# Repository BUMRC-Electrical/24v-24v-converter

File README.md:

<!-- kicad_template/README.md -->

<div align="center">
    
</div>

## 24V-24V 35 Amp Converter

This repository contains all documentation and files for the custom 24V Converter.

## File Structure

- ```/kicad/``` contains all of the KiCad 10.0 project files
- ```/datasheets/``` contains all of the .pdf files for the important components
- ```/calculations/``` contains significant calculations that led to a component choice or value choice
- ```/cad/``` currently contains no files
- ```24V_BOM.xlsx``` contains all components, quantities, and links to purchase

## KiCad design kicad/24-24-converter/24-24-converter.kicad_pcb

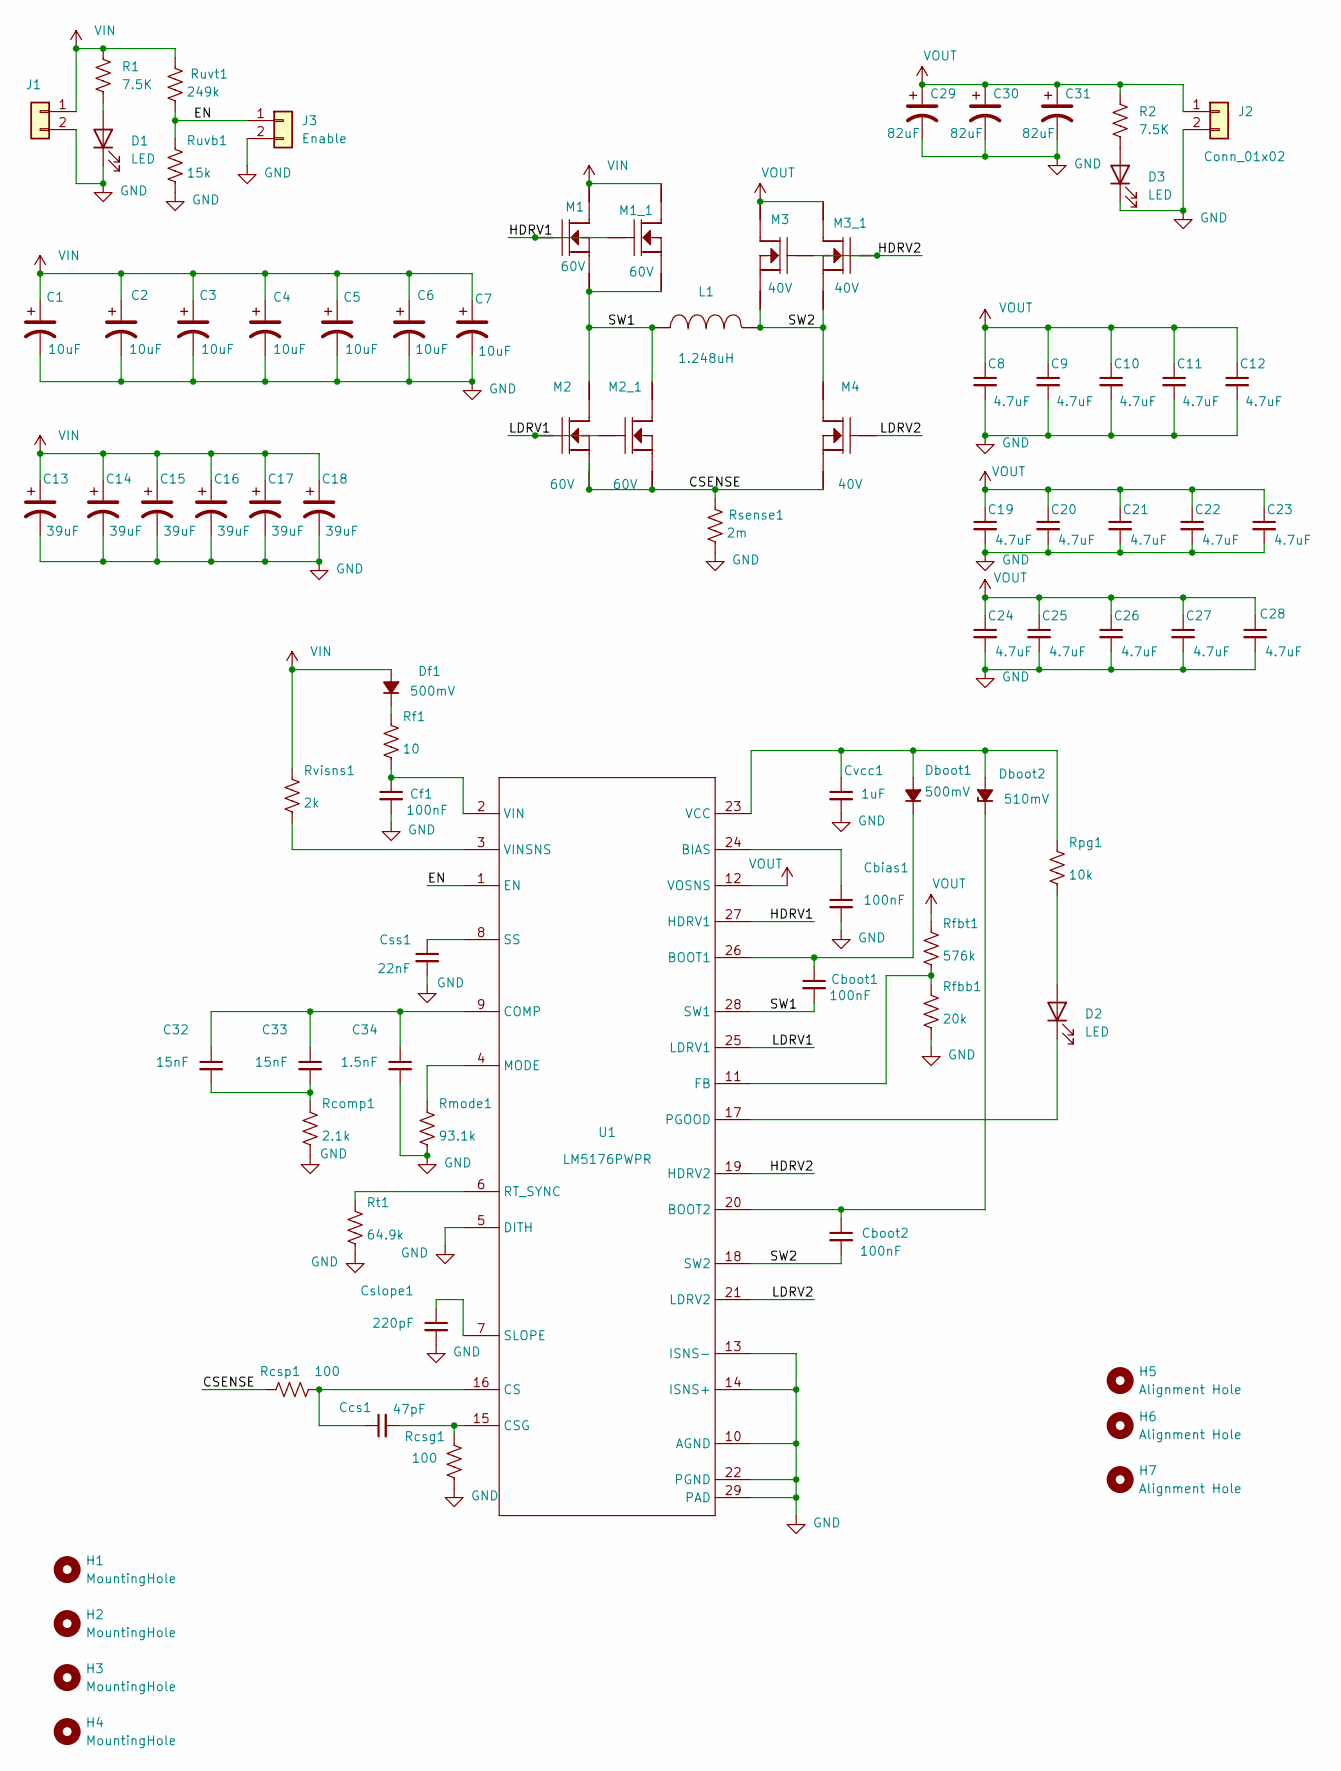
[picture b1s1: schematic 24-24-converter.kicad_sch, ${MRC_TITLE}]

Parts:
C1, C2, C3, C4, C5, C6, C7: 50SVPF10M; Cbulk_CAP_B6-SVPK_PAN; MANUFACTURER PART NUMBER 50SVPF10M
C8, C9, C10, C11, C12, C19, C20, C21, C22, C23, C24, C25, C26, C27, C28: MSASU21GBB5475KTNA01; C_0805_2012Metric_Pad1.18x1.45mm_HandSolder; MANUFACTURER PART NUMBER MSASU21GBB5475KTNA01
C13, C14, C15, C16, C17, C18: 50SVPF39M; Cin_50SVPF39M; MANUFACTURER PART NUMBER 50SVPF39M
C29, C30, C31: 35SVPF82M; PCAP_SVP_E12_PAN; MANUFACTURER PART NUMBER 35SVPF82M
C32, C33: MSASH21GSB7153MTNA01; C_0805_2012Metric_Pad1.18x1.45mm_HandSolder; MANUFACTURER PART NUMBER MSASH21GSB7153MTNA01
C34: GRM2195C1H152JA01D; C_0805_2012Metric_Pad1.18x1.45mm_HandSolder; MANUFACTURER PART NUMBER GRM2195C1H152JA01D
Cbias1: C0805C104M5RACTU; C_0805_2012Metric_Pad1.18x1.45mm_HandSolder; MANUFACTURER PART NUMBER C0805C104M5RACTU
Cboot1, Cboot2: 06033C104KAT2A; C_0805_2012Metric_Pad1.18x1.45mm_HandSolder; MANUFACTURER PART NUMBER 06033C104KAT2A
Ccs1: 06035A470JAT2A; C_0805_2012Metric_Pad1.18x1.45mm_HandSolder; MANUFACTURER PART NUMBER 06035A470JAT2A
Cf1: CGA3E2X7R1H104K080AA; C_0805_2012Metric_Pad1.18x1.45mm_HandSolder; MANUFACTURER PART NUMBER CGA3E2X7R1H104K080AA
Cslope1: CL10C221JB8NNNC; C_0603_1608Metric_Pad1.08x0.95mm_HandSolder; MANUFACTURER PART NUMBER CL10C221JB8NNNC
Css1: C2012C0G1H223K125AA; C_0603_1608Metric_Pad1.08x0.95mm_HandSolder; MANUFACTURER PART NUMBER C2012C0G1H223K125AA
Cvcc1: EMK107B7105KA-T; C_0603_1608Metric_Pad1.08x0.95mm_HandSolder; MANUFACTURER PART NUMBER EMK107B7105KA-T
D1, D2, D3: LED; LED_1206_3216Metric_Pad1.42x1.75mm_HandSolder
Dboot1: GENERIC_DIODE; Diode_BAS16HT1G; MANUFACTURER PART NUMBER GENERIC_DIODE
Dboot2: CDBK0540-HF; Shottkey_MBR0540-TP; MANUFACTURER PART NUMBER CDBK0540-HF
Df1: GENERIC_DIODE; Diode_BAS16HT1G; MANUFACTURER PART NUMBER GENERIC_DIODE
H1, H2, H3, H4: MountingHole; MountingHole_2.5mm
H5, H6, H7: Alignment Hole
J1, J2: Conn_01x02; AMASS_XT60-F_1x02_P7.20mm_Vertical
J3: Enable; PinHeader_1x02_P1.00mm_Vertical
L1: GENERIC_INDUCTOR; L-SRP1770TA-100M_1; MANUFACTURER PART NUMBER GENERIC_INDUCTOR
M1, M1_1, M2, M2_1: CSD18540Q5B; MOSFET_CSD18540Q5B; MANUFACTURER PART NUMBER CSD18540Q5B
M3, M3_1, M4: GENERIC_MOSFET_N; MOSFET_CSD18540Q5B; MANUFACTURER PART NUMBER GENERIC_MOSFET_N
R1, R2: 7.5K; R_1206_3216Metric_Pad1.30x1.75mm_HandSolder
Rcomp1: CRCW04022K10FKED; R_0805_2012Metric_Pad1.20x1.40mm_HandSolder; MANUFACTURER PART NUMBER CRCW04022K10FKED
Rcsg1: CRCW0603100RFKEA; R_0603_1608Metric_Pad0.98x0.95mm_HandSolder; MANUFACTURER PART NUMBER CRCW0603100RFKEA
Rcsp1: CRCW0603100RFKEA; R_0603_1608Metric_Pad0.98x0.95mm_HandSolder; MANUFACTURER PART NUMBER CRCW0603100RFKEA
Rf1: RC0603FR-0710RL; R_0805_2012Metric_Pad1.20x1.40mm_HandSolder; MANUFACTURER PART NUMBER RC0603FR-0710RL
Rfbb1: RC0603FR-0720KL; R_0603_1608Metric_Pad0.98x0.95mm_HandSolder; MANUFACTURER PART NUMBER RC0603FR-0720KL
Rfbt1: RC0603FR-07576KL; R_0603_1608Metric_Pad0.98x0.95mm_HandSolder; MANUFACTURER PART NUMBER RC0603FR-07576KL
Rmode1: RC0603FR-0793K1L; R_0603_1608Metric_Pad0.98x0.95mm_HandSolder; MANUFACTURER PART NUMBER RC0603FR-0793K1L
Rpg1: RC0603FR-0710KL; R_0603_1608Metric_Pad0.98x0.95mm_HandSolder; MANUFACTURER PART NUMBER RC0603FR-0710KL
Rsense1: FCSL64R002GER; RSense_FCSL64R002GER; MANUFACTURER PART NUMBER FCSL64R002GER
Rt1: CRCW040264K9FKED; R_0603_1608Metric_Pad0.98x0.95mm_HandSolder; MANUFACTURER PART NUMBER CRCW040264K9FKED
Ruvb1: CRCW040215K0FKED; R_0603_1608Metric_Pad0.98x0.95mm_HandSolder; MANUFACTURER PART NUMBER CRCW040215K0FKED
Ruvt1: CRCW0402249KFKED; R_0603_1608Metric_Pad0.98x0.95mm_HandSolder; MANUFACTURER PART NUMBER CRCW0402249KFKED
Rvisns1: CRCW04022K00FKED; R_0603_1608Metric_Pad0.98x0.95mm_HandSolder; MANUFACTURER PART NUMBER CRCW04022K00FKED
U1: LM5176PWPR; MANUFACTURER PART NUMBER LM5176PWPR

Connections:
/CSENSE: M2.1 (Source), M2.2 (Source), M2.3 (Source), M2_1.1 (Source), M2_1.2 (Source), M2_1.3 (Source), M4.1 (Source), M4.2 (Source), M4.3 (Source), Rcsp1.1, Rsense1.1
/EN: J3.1, Ruvb1.1, Ruvt1.2, U1.1 (EN)
/HDRV1: M1.4 (Gate), M1_1.4 (Gate), U1.27 (HDRV1)
/HDRV2: M3.4 (Gate), M3_1.4 (Gate), U1.19 (HDRV2)
/LDRV1: M2.4 (Gate), M2_1.4 (Gate), U1.25 (LDRV1)
/LDRV2: M4.4 (Gate), U1.21 (LDRV2)
/SW1: Cboot1.2, L1.1, M1.1 (Source), M1.2 (Source), M1.3 (Source), M1_1.1 (Source), M1_1.2 (Source), M1_1.3 (Source), M2.5 (Drain), M2.6 (Drain), M2.7 (Drain), M2.8 (Drain), M2.9 (Drain), M2_1.5 (Drain), M2_1.6 (Drain), M2_1.7 (Drain), M2_1.8 (Drain), M2_1.9 (Drain), U1.28 (SW1)
/SW2: Cboot2.2, L1.2, M3.1 (Source), M3.2 (Source), M3.3 (Source), M3_1.1 (Source), M3_1.2 (Source), M3_1.3 (Source), M4.5 (Drain), M4.6 (Drain), M4.7 (Drain), M4.8 (Drain), M4.9 (Drain), U1.18 (SW2)
GND: C1.2, C2.2, C3.2, C4.2, C5.2, C6.2, C7.2, C8.2, C9.2, C10.2, C11.2, C12.2, C13.2, C14.2, C15.2, C16.2, C17.2, C18.2, C19.2, C20.2, C21.2, C22.2, C23.2, C24.2, C25.2, C26.2, C27.2, C28.2, C29.2, C30.2, C31.2, C34.2, Cbias1.2, Cf1.2, Cslope1.2, Css1.2, Cvcc1.2, D1.1 (K), D3.1 (K), J1.2, J2.2, J3.2, Rcomp1.2, Rcsg1.2, Rfbb1.2, Rmode1.2, Rsense1.2, Rt1.2, Ruvb1.2, U1.5 (DITH), U1.10 (AGND), U1.13 (ISNS-), U1.14 (ISNS+), U1.22 (PGND), U1.29 (PAD)
unnamed: C32.2, C33.2, Rcomp1.1
unnamed: D1.2 (A), R1.2
unnamed: D2.2 (A), Rpg1.2
unnamed: D2.1 (K), U1.17 (PGOOD)
unnamed: D3.2 (A), R2.2
unnamed: Cvcc1.1, Dboot1.2 (A), Dboot2.2 (A), Rpg1.1, U1.23 (VCC)
unnamed: Cboot1.1, Dboot1.1 (K), U1.26 (BOOT1)
unnamed: Cboot2.1, Dboot2.1 (K), U1.20 (BOOT2)
unnamed: Df1.1 (K), Rf1.1
unnamed: Cbias1.1, U1.24 (BIAS)
unnamed: C32.1, C33.1, C34.1, U1.9 (COMP)
unnamed: Ccs1.1, Rcsp1.2, U1.16 (CS)
unnamed: Ccs1.2, Rcsg1.1, U1.15 (CSG)
unnamed: Rfbb1.1, Rfbt1.2, U1.11 (FB)
unnamed: Rmode1.1, U1.4 (MODE)
unnamed: Rt1.1, U1.6 (RT_SYNC)
unnamed: Cslope1.1, U1.7 (SLOPE)
unnamed: Css1.1, U1.8 (SS)
unnamed: Cf1.1, Rf1.2, U1.2 (VIN)
unnamed: Rvisns1.2, U1.3 (VINSNS)
VIN: C1.1, C2.1, C3.1, C4.1, C5.1, C6.1, C7.1, C13.1, C14.1, C15.1, C16.1, C17.1, C18.1, Df1.2 (A), J1.1, M1.5 (Drain), M1.6 (Drain), M1.7 (Drain), M1.8 (Drain), M1.9 (Drain), M1_1.5 (Drain), M1_1.6 (Drain), M1_1.7 (Drain), M1_1.8 (Drain), M1_1.9 (Drain), R1.1, Ruvt1.1, Rvisns1.1
VOUT: C8.1, C9.1, C10.1, C11.1, C12.1, C19.1, C20.1, C21.1, C22.1, C23.1, C24.1, C25.1, C26.1, C27.1, C28.1, C29.1, C30.1, C31.1, J2.1, M3.5 (Drain), M3.6 (Drain), M3.7 (Drain), M3.8 (Drain), M3.9 (Drain), M3_1.5 (Drain), M3_1.6 (Drain), M3_1.7 (Drain), M3_1.8 (Drain), M3_1.9 (Drain), R2.1, Rfbt1.1, U1.12 (VOSNS)

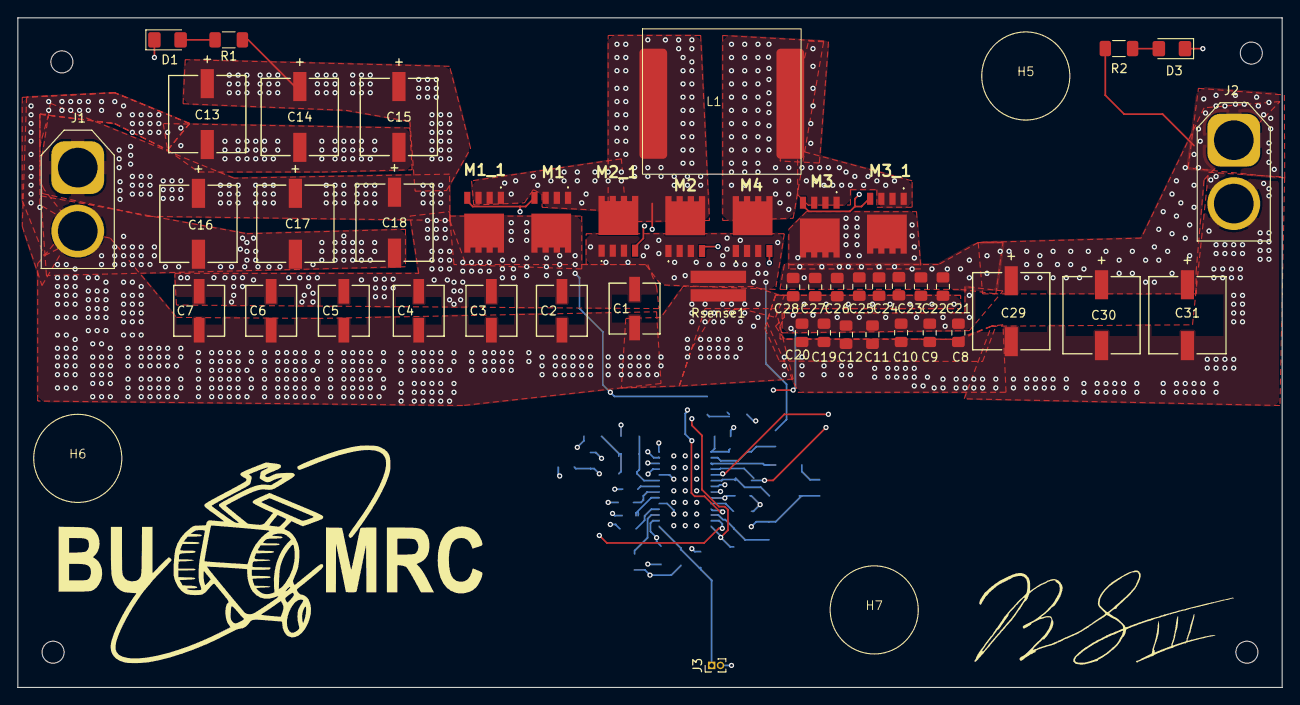
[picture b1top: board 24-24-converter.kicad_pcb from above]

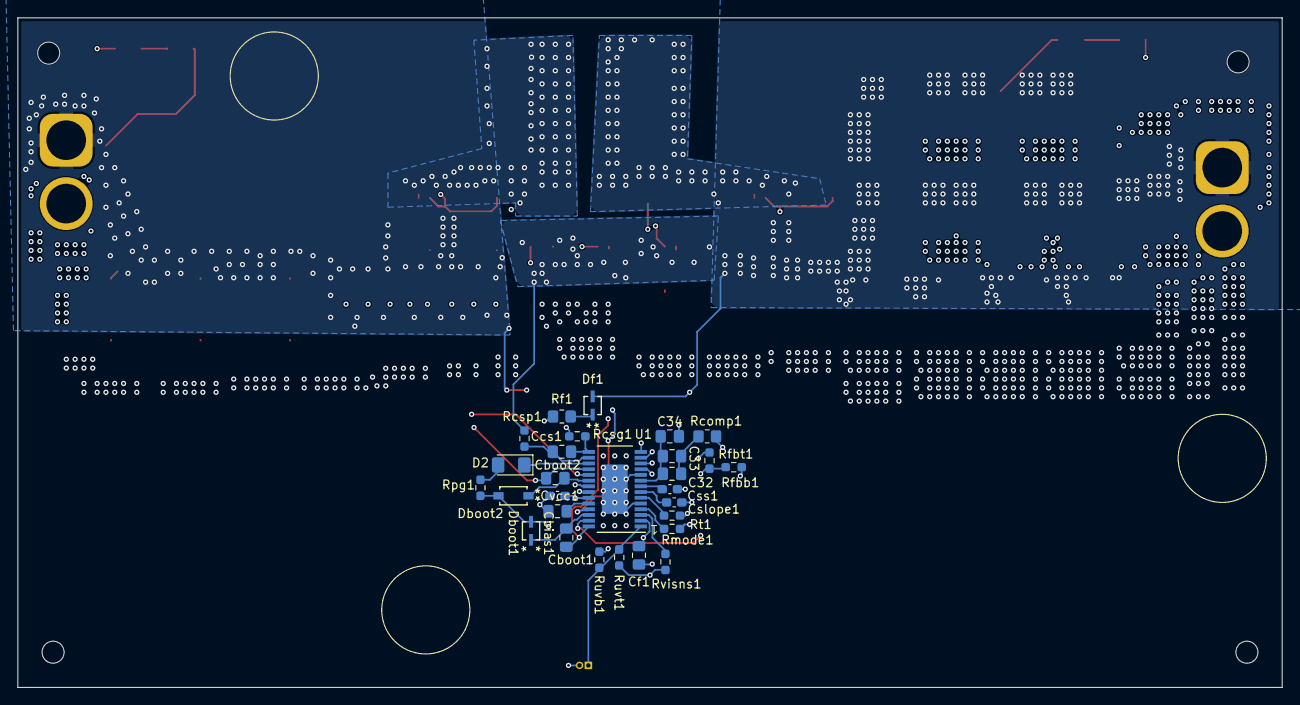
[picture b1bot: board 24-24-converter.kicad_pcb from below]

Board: 4 copper layers, 143.5 x 76.0 mm, 82 parts (28 on the bottom side), 31 nets.

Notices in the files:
parts and their libraries:
Copyright 2016 Accelerated Designs. All rights reserved.
